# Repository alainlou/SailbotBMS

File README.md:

# SailbotBMS
bq77519-based battery management system for UWSailbot

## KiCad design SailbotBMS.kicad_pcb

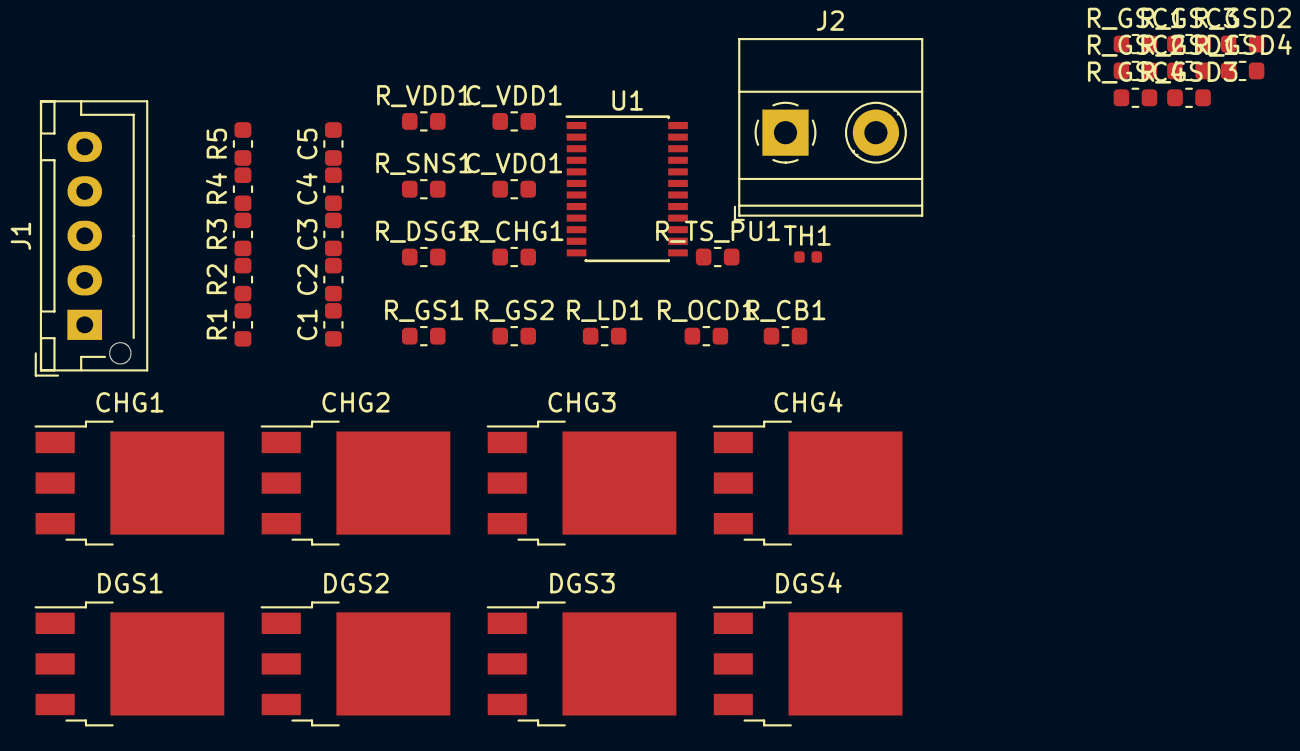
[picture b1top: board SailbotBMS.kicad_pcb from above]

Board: 2 copper layers, 42 parts (0 on the bottom side), 24 nets, no tracks yet.

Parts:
C1, C2, C3, C4, C5: 1uF; C_0603_1608Metric
CHG1, CHG2, CHG3, CHG4: 4V; TO-252-3_TabPin2
C_VDD1: 1uF; C_0603_1608Metric
C_VDO1: 1uF; C_0603_1608Metric
DGS1, DGS2, DGS3, DGS4: 4V; TO-252-3_TabPin2
J1: Conn_01x05_Female; JST_XH_B05B-XH-AM_1x05_P2.50mm_Vertical
J2: Conn_01x02; TerminalBlock_Phoenix_MKDS-1,5-2-5.08_1x02_P5.08mm_Horizont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
R1, R2, R3, R4, R5: 33; R_0603_1608Metric
R_CB1: 10k; R_0603_1608Metric
R_CHG1: 0; R_0603_1608Metric
R_DSG1: 0; R_0603_1608Metric
R_GS1, R_GS2: 1M; R_0603_1608Metric
R_GSC1, R_GSC2, R_GSC3, R_GSC4: 1M; R_0603_1608Metric
R_GSD1, R_GSD2, R_GSD3, R_GSD4: 1M; R_0603_1608Metric
R_LD1: 470k; R_0603_1608Metric
R_OCD1: 196k; R_0603_1608Metric
R_SNS1: 4m; R_0603_1608Metric
R_TS_PU1: 10k; R_0603_1608Metric
R_VDD1: 1k; R_0603_1608Metric
TH1: 103AT, 10k; R_0402_1005Metric
U1: BQ77915; TSSOP-24_4.4x7.8mm_P0.65mm

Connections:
unnamed: C1.2, R1.1, U1.8
unnamed: C2.1, C3.2, R2.1, U1.7
unnamed: C3.1, C4.2, R3.1, U1.6
unnamed: C4.1, C5.2, R4.1, U1.5
unnamed: C5.1, R5.1, U1.3, U1.4
unnamed: CHG1.1, CHG2.1, CHG3.1, CHG4.1, DGS1.1, DGS2.1, DGS3.1, DGS4.1
unnamed: CHG1.2, CHG2.2, CHG3.2, CHG4.2, R_CHG1.2, R_GS2.1, R_GSC1.1, R_GSC2.1, R_GSC3.1, R_GSC4.1
unnamed: C_VDD1.1, R_VDD1.1, U1.1
unnamed: C_VDO1.1, U1.2, U1.20
unnamed: DGS1.2, DGS2.2, DGS3.2, DGS4.2, R_DSG1.2, R_GS1.1, R_GSD1.1, R_GSD2.1, R_GSD3.1, R_GSD4.1
unnamed: DGS1.3, DGS2.3, DGS3.3, DGS4.3, R_GS1.2, R_GSD1.2, R_GSD2.2, R_GSD3.2, R_GSD4.2, R_SNS1.1, U1.11
unnamed: J1.1, R1.2, R_SNS1.2, U1.9, U1.10
unnamed: J1.2, R2.2
unnamed: J1.3, R3.2
unnamed: J1.4, R4.2
unnamed: R_CB1.1, U1.16
unnamed: R_CHG1.1, U1.13
unnamed: R_DSG1.1, U1.12
unnamed: R_LD1.1, U1.14
unnamed: R_OCD1.1, U1.17
unnamed: R_TS_PU1.1, U1.19
unnamed: R_TS_PU1.2, TH1.2, U1.18
PACK+: J1.5, J2.1, R5.2, R_VDD1.2, U1.22
PACK-: C1.1, C2.2, CHG1.3, CHG2.3, CHG3.3, CHG4.3, C_VDD1.2, C_VDO1.2, J2.2, R_CB1.2, R_GS2.2, R_GSC1.2, R_GSC2.2, R_GSC3.2, R_GSC4.2, R_LD1.2, R_OCD1.2, TH1.1, U1.23, U1.24

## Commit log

2019-07-09 add bq77915
2019-07-09 SNAPSHOT 0.1.0 - bq77915.lib file first iteration
2019-07-09 rename BQ77915
2019-07-09 update .gitignore and delete backup files
2019-07-09 renaming and project organization
2019-07-09 good morning fixes
2019-07-16 initial inplementation functionality
2019-07-24 end of day commit
2019-07-30 assign thermistor footprint
2019-07-30 still incorrect footprint for transistor
2019-07-30 change footprint for transistors - maybe still not right
2019-07-30 initial layout
2019-07-30 afternoon check-in
2019-07-30 real estate is valuable
2019-07-30 renaming so it makes more sense to me
2019-07-31 select the correct DPAK footprint and put the transistors in parallel, not series
2019-08-05 PACK- in our case is GNDREF
